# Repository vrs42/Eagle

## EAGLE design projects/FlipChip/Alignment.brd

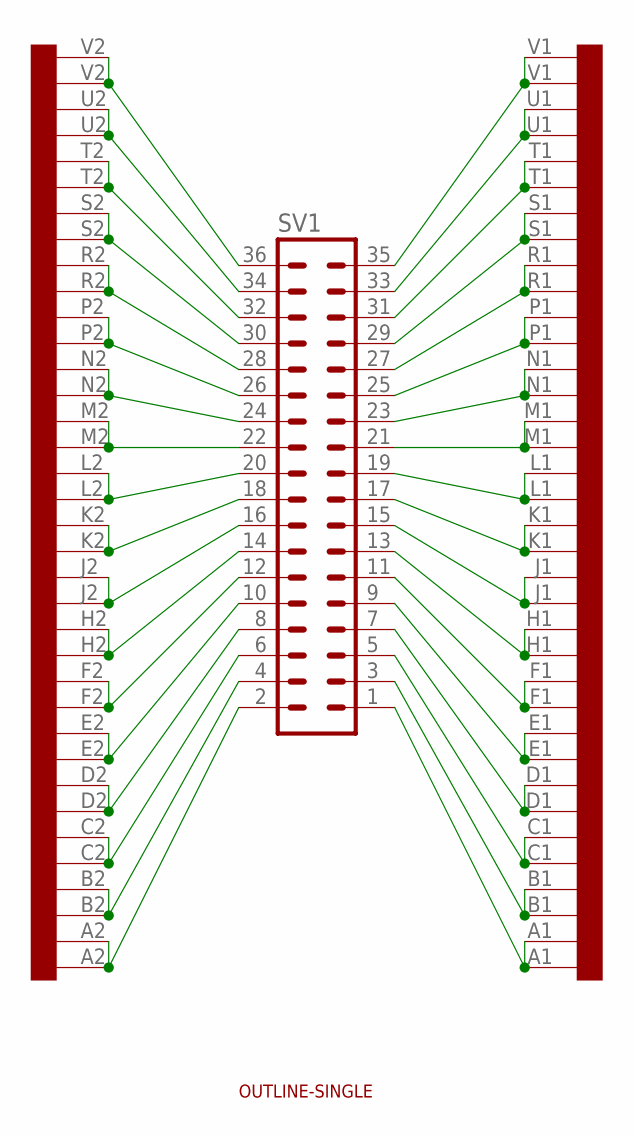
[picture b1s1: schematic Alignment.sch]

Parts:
EDGE: EDGE-2ECONO; ECONOSINGLE
SV1: MA18-2
U$1: EDGE-2CONNECTOR; EDGE-CON2
U$3: OUTLINE-SINGLE; SINGLE

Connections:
unnamed: EDGE.V2, SV1.36, U$1.V2
unnamed: EDGE.U2, SV1.34, U$1.U2
unnamed: EDGE.T2, SV1.32, U$1.T2
unnamed: EDGE.S2, SV1.30, U$1.S2
unnamed: EDGE.R2, SV1.28, U$1.R2
unnamed: EDGE.P2, SV1.26, U$1.P2
unnamed: EDGE.N2, SV1.24, U$1.N2
unnamed: EDGE.M2, SV1.22, U$1.M2
unnamed: EDGE.L2, SV1.20, U$1.L2
unnamed: EDGE.K2, SV1.18, U$1.K2
unnamed: EDGE.J2, SV1.16, U$1.J2
unnamed: EDGE.H2, SV1.14, U$1.H2
unnamed: EDGE.F2, SV1.12, U$1.F2
unnamed: EDGE.E2, SV1.10, U$1.E2
unnamed: EDGE.D2, SV1.8, U$1.D2
unnamed: EDGE.C2, SV1.6, U$1.C2
unnamed: EDGE.B2, SV1.4, U$1.B2
unnamed: EDGE.A2, SV1.2, U$1.A2
unnamed: EDGE.V1, SV1.35, U$1.V1
unnamed: EDGE.U1, SV1.33, U$1.U1
unnamed: EDGE.T1, SV1.31, U$1.T1
unnamed: EDGE.S1, SV1.29, U$1.S1
unnamed: EDGE.R1, SV1.27, U$1.R1
unnamed: EDGE.P1, SV1.25, U$1.P1
unnamed: EDGE.N1, SV1.23, U$1.N1
unnamed: EDGE.M1, SV1.21, U$1.M1
unnamed: EDGE.L1, SV1.19, U$1.L1
unnamed: EDGE.K1, SV1.17, U$1.K1
unnamed: EDGE.J1, SV1.15, U$1.J1
unnamed: EDGE.H1, SV1.13, U$1.H1
unnamed: EDGE.F1, SV1.11, U$1.F1
unnamed: EDGE.E1, SV1.9, U$1.E1
unnamed: EDGE.D1, SV1.7, U$1.D1
unnamed: EDGE.C1, SV1.5, U$1.C1
unnamed: EDGE.B1, SV1.3, U$1.B1
unnamed: EDGE.A1, SV1.1, U$1.A1

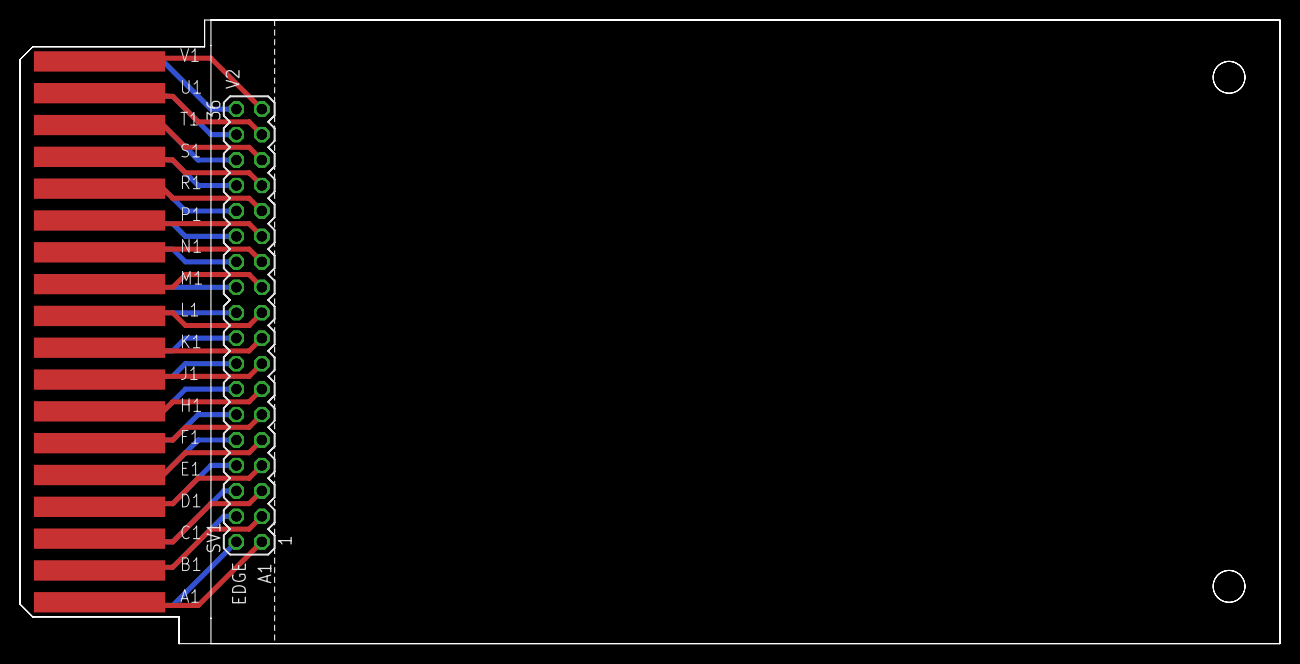
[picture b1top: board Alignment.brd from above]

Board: 2 copper layers, 125.7 x 62.2 mm, 4 parts (0 on the bottom side), 36 nets.

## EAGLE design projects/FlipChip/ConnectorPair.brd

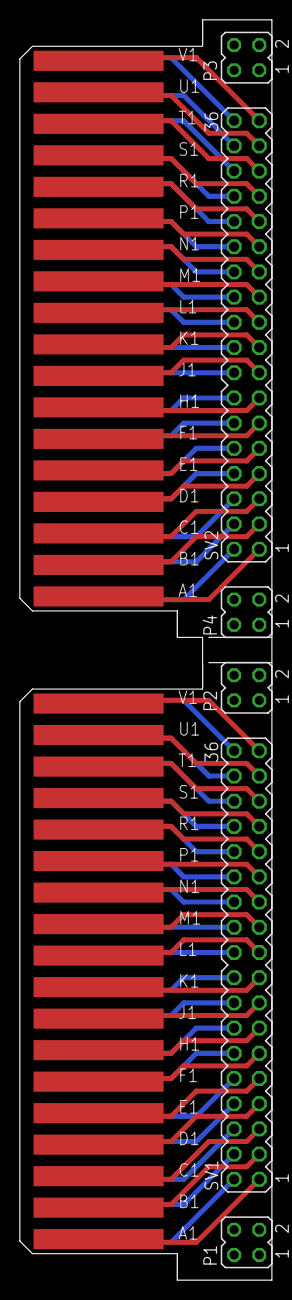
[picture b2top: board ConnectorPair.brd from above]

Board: 2 copper layers, 25.4 x 127.0 mm, 8 parts (0 on the bottom side), 72 nets.

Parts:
P1, P2, P3, P4: JP2Q
SV1, SV2: MA18-2
U$1, U$2: EDGE-CON2

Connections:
unnamed: SV1.36, U$1.V2
unnamed: SV1.34, U$1.U2
unnamed: SV1.32, U$1.T2
unnamed: SV1.30, U$1.S2
unnamed: SV1.28, U$1.R2
unnamed: SV1.26, U$1.P2
unnamed: SV1.24, U$1.N2
unnamed: SV1.22, U$1.M2
unnamed: SV1.20, U$1.L2
unnamed: SV1.18, U$1.K2
unnamed: SV1.16, U$1.J2
unnamed: SV1.14, U$1.H2
unnamed: SV1.12, U$1.F2
unnamed: SV1.10, U$1.E2
unnamed: SV1.8, U$1.D2
unnamed: SV1.6, U$1.C2
unnamed: SV1.4, U$1.B2
unnamed: SV1.2, U$1.A2
unnamed: SV1.35, U$1.V1
unnamed: SV1.33, U$1.U1
unnamed: SV1.31, U$1.T1
unnamed: SV1.29, U$1.S1
unnamed: SV1.27, U$1.R1
unnamed: SV1.25, U$1.P1
unnamed: SV1.23, U$1.N1
unnamed: SV1.21, U$1.M1
unnamed: SV1.19, U$1.L1
unnamed: SV1.17, U$1.K1
unnamed: SV1.15, U$1.J1
unnamed: SV1.13, U$1.H1
unnamed: SV1.11, U$1.F1
unnamed: SV1.9, U$1.E1
unnamed: SV1.7, U$1.D1
unnamed: SV1.5, U$1.C1
unnamed: SV1.3, U$1.B1
unnamed: SV1.1, U$1.A1
unnamed: SV2.36, U$2.V2
unnamed: SV2.34, U$2.U2
unnamed: SV2.32, U$2.T2
unnamed: SV2.30, U$2.S2
unnamed: SV2.28, U$2.R2
unnamed: SV2.26, U$2.P2
unnamed: SV2.24, U$2.N2
unnamed: SV2.22, U$2.M2
unnamed: SV2.20, U$2.L2
unnamed: SV2.18, U$2.K2
unnamed: SV2.16, U$2.J2
unnamed: SV2.14, U$2.H2
unnamed: SV2.12, U$2.F2
unnamed: SV2.10, U$2.E2
unnamed: SV2.8, U$2.D2
unnamed: SV2.6, U$2.C2
unnamed: SV2.4, U$2.B2
unnamed: SV2.2, U$2.A2
unnamed: SV2.35, U$2.V1
unnamed: SV2.33, U$2.U1
unnamed: SV2.31, U$2.T1
unnamed: SV2.29, U$2.S1
unnamed: SV2.27, U$2.R1
unnamed: SV2.25, U$2.P1
unnamed: SV2.23, U$2.N1
unnamed: SV2.21, U$2.M1
unnamed: SV2.19, U$2.L1
unnamed: SV2.17, U$2.K1
unnamed: SV2.15, U$2.J1
unnamed: SV2.13, U$2.H1
unnamed: SV2.11, U$2.F1
unnamed: SV2.9, U$2.E1
unnamed: SV2.7, U$2.D1
unnamed: SV2.5, U$2.C1
unnamed: SV2.3, U$2.B1
unnamed: SV2.1, U$2.A1
